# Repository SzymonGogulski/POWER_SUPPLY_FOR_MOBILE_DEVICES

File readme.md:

**English version at the bottom.**
#  
Projekt przedstawia przykład zasilacza dla urządzeń mobilnych. Autor Szymon Gogulski
### Główne założenia projektów
1. Zasilacz jest w stanie dostarczyć 1.8A prądu ciągłego do układu zasilanego,
2. Układ zasilany jest z jednego ogniwa LIT-ION 18650.

### Pozostałe zadania
1. Wykonaj testy rzeczywistego urządzenia.
2. Przygotuj dokumentację z opisem.

### Opracowane na podstawie
1. [Battery Charge and System Load Sharing Management With MCP73871 AN1260](https://ww1.microchip.com/downloads/en/Appnotes/01260B.pdf)
2. [MAX17048-MAX17049 Datasheet](https://www.analog.com/media/en/technical-documentation/data-sheets/max17048-max17049.pdf)
3. [MCP73871 Datasheet](https://ww1.microchip.com/downloads/en/DeviceDoc/MCP73871-Data-Sheet-20002090E.pdf)
4. [TPS61022 Datasheet](https://www.ti.com/lit/gpn/TPS61022)
5. [Texas Instruments Power Designer](https://webench.ti.com/power-designer/)
6. [Adafruit Icharging](https://learn.adafruit.com/minty-boost/icharging)
***

### Schemat elektronicznych

### Płytka PCB

### Płytka PCB 3D

### Płytka PCB 3D

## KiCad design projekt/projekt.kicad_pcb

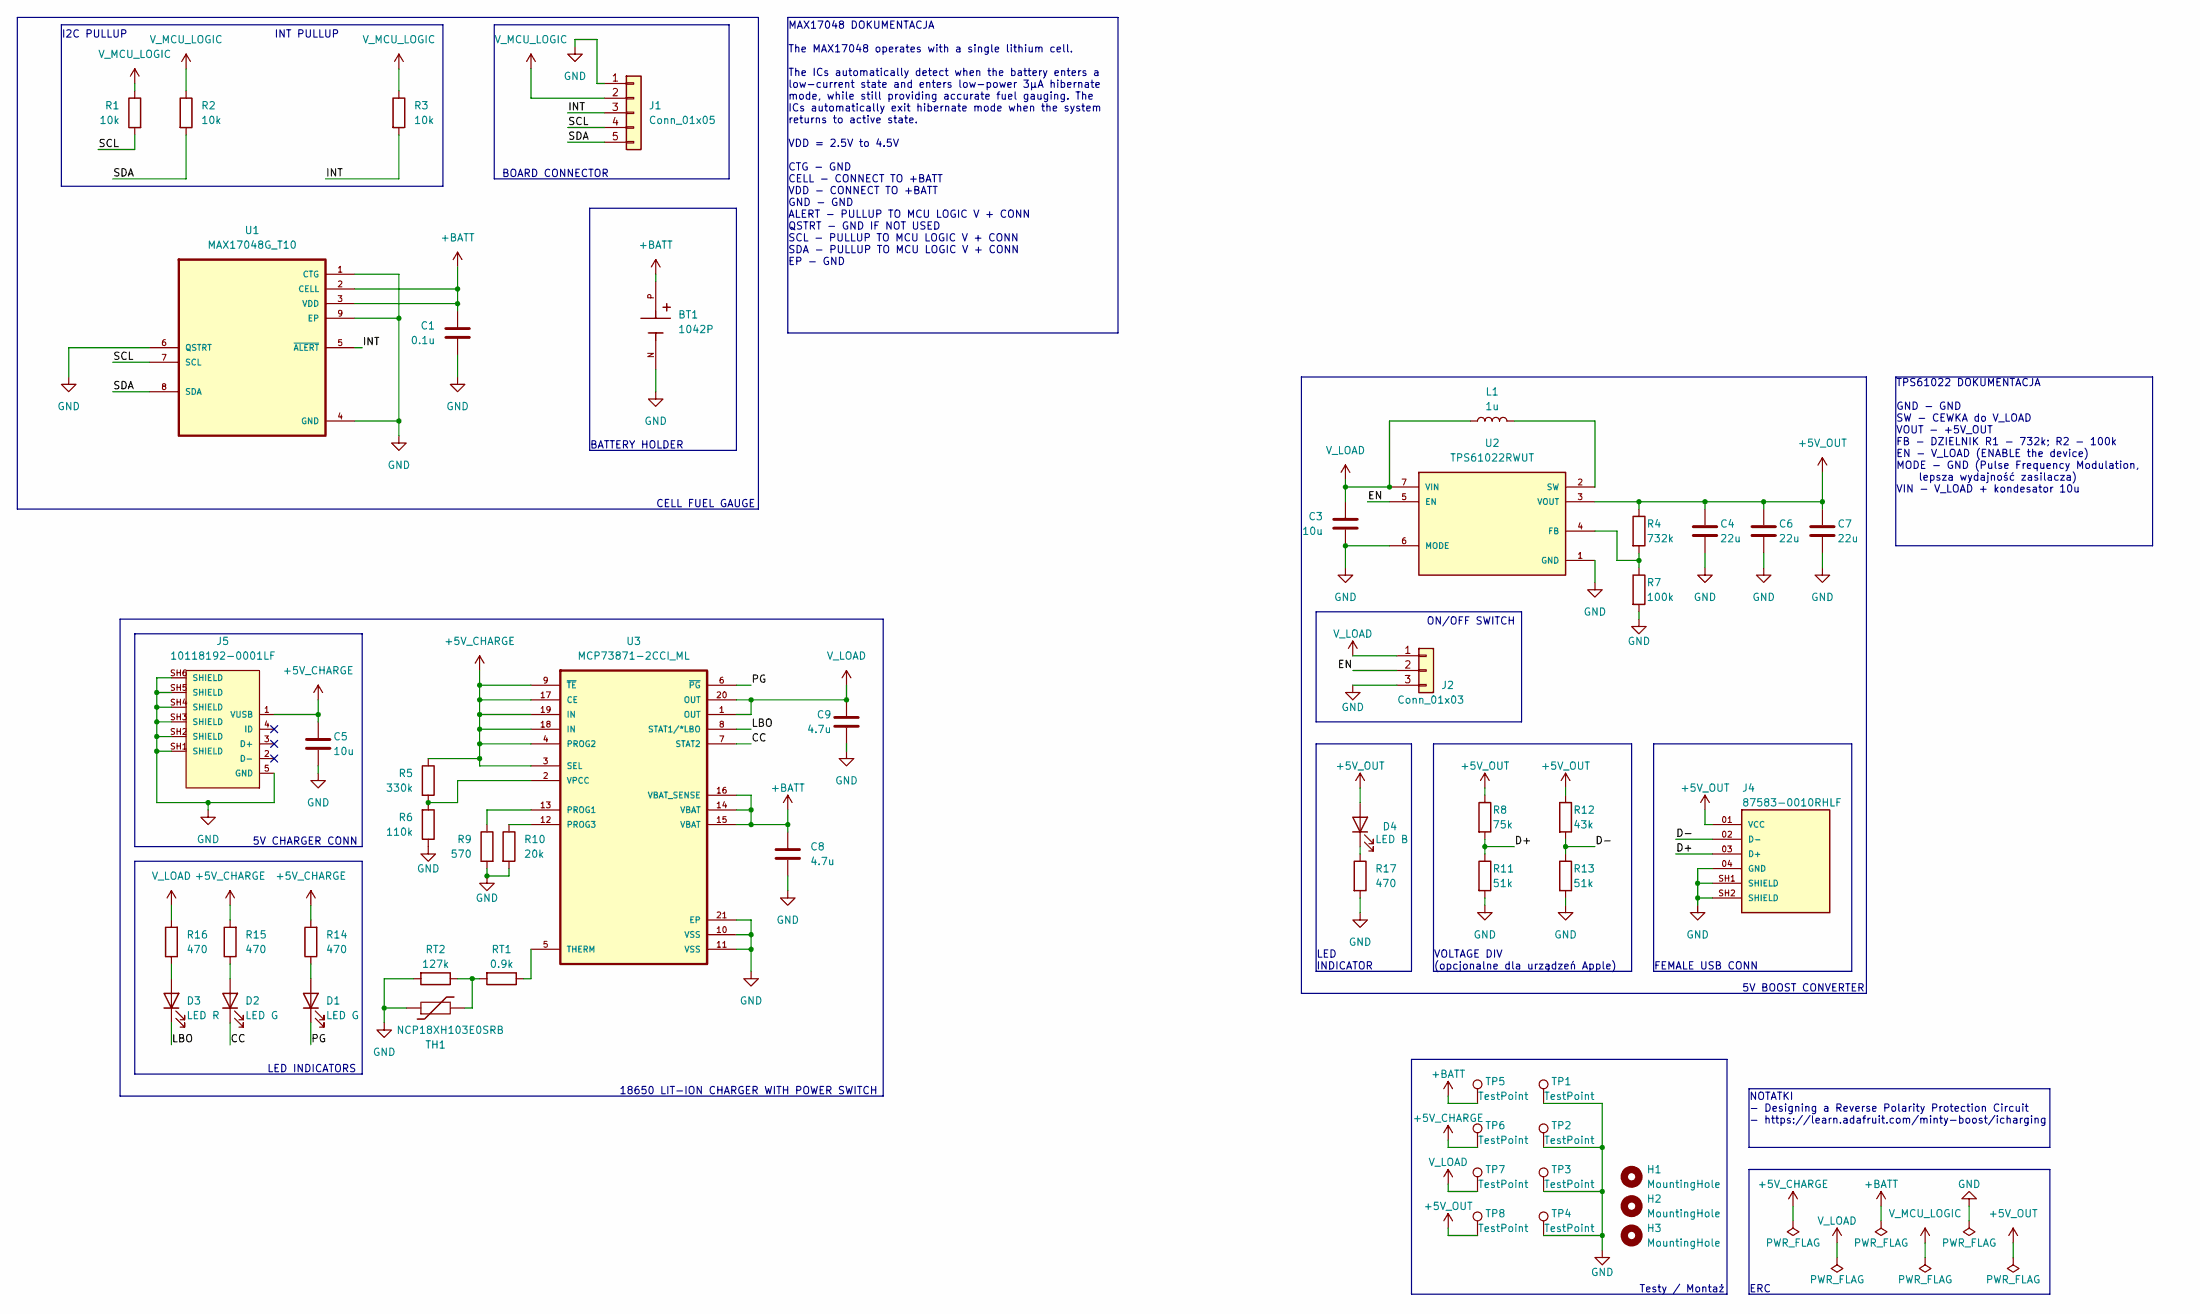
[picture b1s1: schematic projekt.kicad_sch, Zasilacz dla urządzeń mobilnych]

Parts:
BT1: 1042P; BAT_1042P; PARTREV E
C1: 0.1u; C_0603_1608Metric
C3, C5: 10u; C_0603_1608Metric
C4, C6, C7: 22u; C_0603_1608Metric
C8, C9: 4.7u; C_0603_1608Metric
D1, D2: LED G; D_0603_1608Metric
D3: LED R; D_0603_1608Metric
D4: LED B; D_0603_1608Metric
H1, H2, H3: MountingHole; MountingHole_2.2mm_M2
J1: Conn_01x05; PinHeader_1x05_P2.54mm_Vertical
J2: Conn_01x03; PinHeader_1x03_P2.54mm_Vertical
J4: 87583-0010RHLF; AMPHENOL_87583-0010RHLF; PARTREV AD
J5: 10118192-0001LF; AMPHENOL_10118192-0001LF; PARTREV B
L1: 1u; WE-TPC_3816
R1, R2, R3: 10k; R_0603_1608Metric
R4: 732k; R_0603_1608Metric
R5: 330k; R_0603_1608Metric
R6: 110k; R_0603_1608Metric
R7: 100k; R_0603_1608Metric
R8: 75k; R_0603_1608Metric
R9: 570; R_0603_1608Metric
R10: 20k; R_0603_1608Metric
R11, R13: 51k; R_0603_1608Metric
R12: 43k; R_0603_1608Metric
R14, R15, R16, R17: 470; R_0603_1608Metric
RT1: 0.9k; R_0603_1608Metric
RT2: 127k; R_0603_1608Metric
TH1: NCP18XH103E0SRB; R_0603_1608Metric
TP1, TP2, TP3, TP4: TestPoint; TestPoint_THTPad_1.0x1.0mm_Drill0.5mm
TP5, TP6, TP7, TP8: TestPoint; TestPoint_THTPad_D1.0mm_Drill0.5mm
U1: MAX17048G_T10; SON50P200X200X80-9N; DigiKey_Part_Number MAX17048G+T10TR-ND
U2: TPS61022RWUT; CONV_TPS61022RWUT; PARTREV January 2020
U3: MCP73871-2CCI_ML; QFN50P400X400X100-21N

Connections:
+5V_CHARGE: C5.1, J5.1 (VUSB), R5.1, R14.2, R15.2, TP6.1, U3.3 (SEL), U3.4 (PROG2), U3.9 (~TE), U3.17 (CE), U3.18 (IN), U3.19 (IN)
+5V_OUT: C4.1, C6.1, C7.1, D4.2 (A), J4.01 (VCC), R4.1, R8.1, R12.1, TP8.1, U2.3 (VOUT)
+BATT: BT1.P, C1.1, C8.1, TP5.1, U1.2 (CELL), U1.3 (VDD), U3.14 (VBAT), U3.15 (VBAT), U3.16 (VBAT_SENSE)
/CC: D2.1 (K), U3.7 (STAT2)
/D+: J4.03 (D+), R8.2, R11.1
/D-: J4.02 (D-), R12.2, R13.1
/EN: J2.2, U2.5 (EN)
/INT: J1.3, R3.2, U1.5 (~ALERT)
/LBO: D3.1 (K), U3.8 (STAT1/*LBO)
/PG: D1.1 (K), U3.6 (~PG)
/SCL: J1.4, R1.2, U1.7 (SCL)
/SDA: J1.5, R2.2, U1.8 (SDA)
GND: BT1.N, C1.2, C3.2, C4.2, C5.2, C6.2, C7.2, C8.2, C9.2, J1.1, J2.3, J4.04 (GND), J4.SH1 (SHIELD), J4.SH2 (SHIELD), J5.5 (GND), J5.SH1 (SHIELD), J5.SH2 (SHIELD), J5.SH3 (SHIELD), J5.SH4 (SHIELD), J5.SH5 (SHIELD), J5.SH6 (SHIELD), R6.1, R7.2, R9.2, R10.2, R11.2, R13.2, R17.2, RT2.2, TH1.1, TP1.1, TP2.1, TP3.1, TP4.1, U1.1 (CTG), U1.4 (GND), U1.6 (QSTRT), U1.9 (EP), U2.1 (GND), U2.6 (MODE), U3.10 (VSS), U3.11 (VSS), U3.21 (EP)
unnamed: D1.2 (A), R14.1
unnamed: D2.2 (A), R15.1
unnamed: D3.2 (A), R16.1
unnamed: D4.1 (K), R17.1
unnamed: RT1.2, RT2.1, TH1.2
unnamed: R4.2, R7.1, U2.4 (FB)
unnamed: L1.2, U2.2 (SW)
unnamed: R9.1, U3.13 (PROG1)
unnamed: R10.1, U3.12 (PROG3)
unnamed: RT1.1, U3.5 (THERM)
unnamed: R5.2, R6.2, U3.2 (VPCC)
V_LOAD: C3.1, C9.1, J2.1, L1.1, R16.2, TP7.1, U2.7 (VIN), U3.1 (OUT), U3.20 (OUT)
V_MCU_LOGIC: J1.2, R1.1, R2.1, R3.1

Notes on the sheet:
BOARD CONNECTOR
I2C PULLUP
ERC
BATTERY HOLDER
5V BOOST CONVERTER
TPS61022 DOKUMENTACJA GND - GND SW - CEWKA do V_LOAD VOUT - +5V_OUT FB - DZIELNIK R1 - 732k; R2 - 100k EN - V_LOAD (ENABLE the device) MODE - GND (Pulse Frequency Modulation, lepsza wydajność zasilacza) VIN - V_LOAD + kondesator 10u
5V CHARGER CONN
18650 LIT-ION CHARGER WITH POWER SWITCH
LED INDICATORS
MAX17048 DOKUMENTACJA The MAX17048 operates with a single lithium cell. The ICs automatically detect when the battery enters a low-current state and enters low-power 3μA hibernate mode, while still providing accurate fuel gauging. The ICs automatically exit hibernate mode when the system returns to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
INT PULLUP
VOLTAGE DIV (opcjonalne dla urządzeń Apple)
FEMALE USB CONN
ON/OFF SWITCH
CELL FUEL GAUGE
Testy / Montaż
LED INDICATOR
NOTATKI - Designing a Reverse Polarity Protection Circuit - https://learn.adafruit.com/minty-boost/icharging

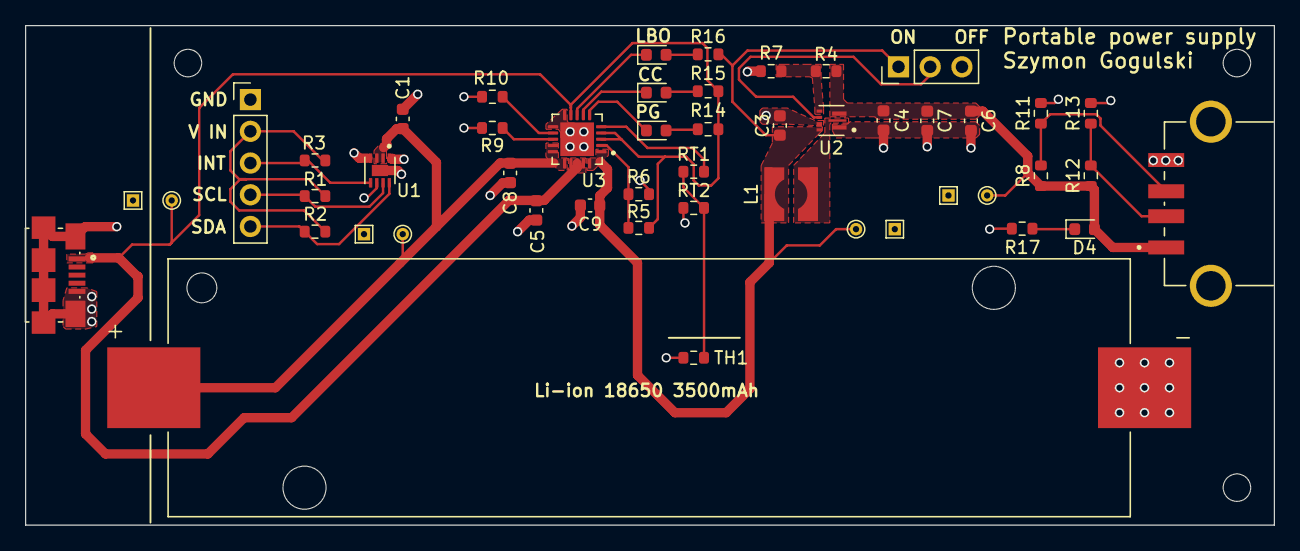
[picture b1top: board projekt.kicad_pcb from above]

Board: 2 copper layers, 100.0 x 40.0 mm, 52 parts (0 on the bottom side), 26 nets.

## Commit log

2025-04-10 MAIN: Initial commit
2025-04-13 MAIN: Work in progress.
2025-04-13 MAIN: PCB work in progress.
2025-04-19 MAIN: wersja pierwsza 19.04.
2025-04-19 MAIN: readme.md update
2025-04-19 MAIN: readme.md update.
2025-04-23 MAIN: 23.04 start wersja 2 - poprawki w schemacie.
2025-04-25 MAIN: Wersja 2: poprawki sieci +5V_CHARGE.
2025-04-27 MAIN: Wersja 2. Sprawdzenie reguł produkcyjnych. Test wykonania u producenta.
2025-04-27 MAIN: wersja 2, dodałem modele 3D.
2025-04-28 MAIN: wersja 2: Poprawiłem termistor, readme update.
2025-05-02 MAIN: wersja 2: koniec, wysłane do produkcji.
2025-05-02 MAIN: readme update.
2025-06-19 poprawki
